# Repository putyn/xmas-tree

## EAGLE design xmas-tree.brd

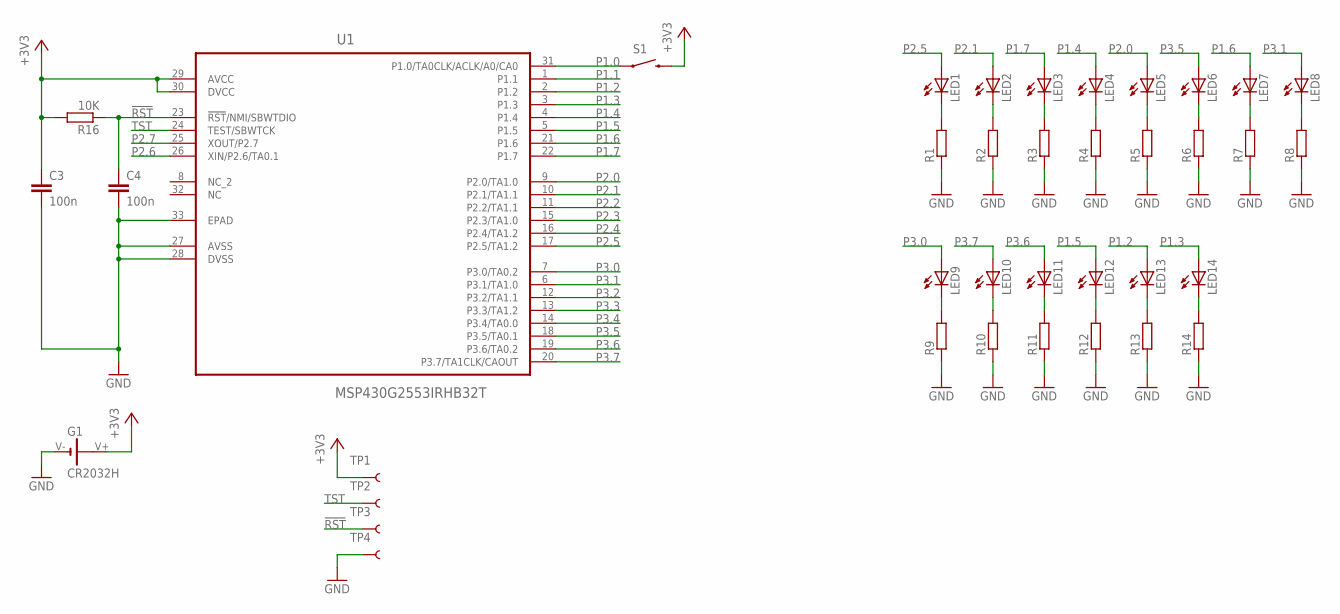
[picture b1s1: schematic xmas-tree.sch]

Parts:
C3, C4: 100n; C0603
G1: CR2032H; CH7410-2032LF
LED1, LED2, LED3, LED4, LED5, LED6, LED7, LED8, LED9, LED10, LED11, LED12, LED13, LED14: LEDCHIPLED_0603; CHIPLED_0603
R1, R2, R3, R4, R5, R6, R7, R8, R9, R10, R11, R12, R13, R14: R-EU_R0603; R0603
R16: 10K; R0603
S1: SWITCH-MOMENTARY-2SMD-REDUNDANT; TACTILE-SWITCH-SMD
TP1: +3V3; PAD.03X.05
TP2: TST; PAD.03X.05
TP3: RST; PAD.03X.05
TP4: GND; PAD.03X.05
U1: MSP430G2553IRHB32T; QFN50P500X500X100-33N

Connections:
!RST!: C4.1, R16.1, TP3.P$1, U1.23 (!RST!/NMI/SBWTDIO)
+3V3: C3.1, G1.V+, R16.2, S1.3 (2), S1.4 (2), TP1.P$1, U1.29 (AVCC), U1.30 (DVCC)
GND: C3.2, C4.2, G1.V-, R1.1, R2.1, R3.1, R4.1, R5.1, R6.1, R7.1, R8.1, R9.1, R10.1, R11.1, R12.1, R13.1, R14.1, TP4.P$1, U1.27 (AVSS), U1.28 (DVSS), U1.33 (EPAD)
unnamed: LED1.C, R1.2
unnamed: LED2.C, R2.2
unnamed: LED3.C, R3.2
unnamed: LED4.C, R4.2
unnamed: LED5.C, R5.2
unnamed: LED6.C, R6.2
unnamed: LED7.C, R7.2
unnamed: LED8.C, R8.2
unnamed: LED9.C, R9.2
unnamed: LED10.C, R10.2
unnamed: LED11.C, R11.2
unnamed: LED12.C, R12.2
unnamed: LED13.C, R13.2
unnamed: LED14.C, R14.2
P1.0: S1.1, S1.2 (1), U1.31 (P1.0/TA0CLK/ACLK/A0/CA0)
P1.1: U1.1 (P1.1)
P1.2: LED13.A, U1.2 (P1.2)
P1.3: LED14.A, U1.3 (P1.3)
P1.4: LED4.A, U1.4 (P1.4)
P1.5: LED12.A, U1.5 (P1.5)
P1.6: LED7.A, U1.21 (P1.6)
P1.7: LED3.A, U1.22 (P1.7)
P2.0: LED5.A, U1.9 (P2.0/TA1.0)
P2.1: LED2.A, U1.10 (P2.1/TA1.1)
P2.2: U1.11 (P2.2/TA1.1)
P2.3: U1.15 (P2.3/TA1.0)
P2.4: U1.16 (P2.4/TA1.2)
P2.5: LED1.A, U1.17 (P2.5/TA1.2)
P2.6: U1.26 (XIN/P2.6/TA0.1)
P2.7: U1.25 (XOUT/P2.7)
P3.0: LED9.A, U1.7 (P3.0/TA0.2)
P3.1: LED8.A, U1.6 (P3.1/TA1.0)
P3.2: U1.12 (P3.2/TA1.1)
P3.3: U1.13 (P3.3/TA1.2)
P3.4: U1.14 (P3.4/TA0.0)
P3.5: LED6.A, U1.18 (P3.5/TA0.1)
P3.6: LED11.A, U1.19 (P3.6/TA0.2)
P3.7: LED10.A, U1.20 (P3.7/TA1CLK/CAOUT)
TST: TP2.P$1, U1.24 (TEST/SBWTCK)

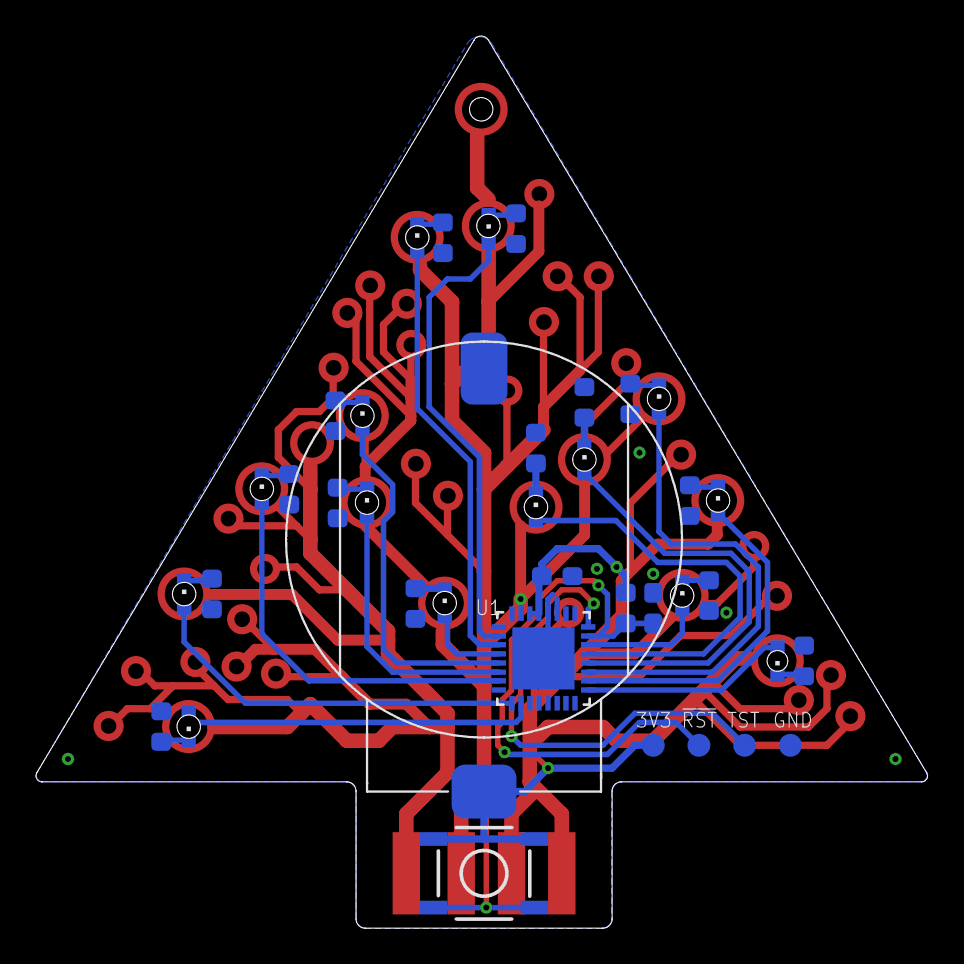
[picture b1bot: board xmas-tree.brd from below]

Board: 2 copper layers, 49.5 x 49.6 mm, 38 parts (38 on the bottom side), 33 nets.

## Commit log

2017-01-12 :space_invader: Added .gitattributes & .gitignore files
2017-01-12 local-repo

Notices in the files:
parts and their libraries:
SparkFun-Electromechanical: Licensing: Creative Commons ShareAlike 4.0 International - https://creativecommons.org/licenses/by-sa/4.0
